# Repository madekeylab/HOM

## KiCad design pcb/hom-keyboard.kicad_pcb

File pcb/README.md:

# HOM-104 풀배열 키보드 PCB (rev 0.1)

사진 속 풀배열 기판을 바탕으로 새로 설계한 KiCad 7 프로젝트입니다.
배열과 기능(키마다 스위치, 다이오드, LED, 저항)은 원본과 같고, MCU와 회로는 새로 설계했습니다.

| 항목 | 내용 |
|---|---|
| 배열 | ANSI 104키 표준 풀배열, 키 간격 19.05 mm |
| 기판 크기 | 434.6 × 129.8 mm, 2층, 모서리 R2 |
| 매트릭스 | 6행 × 21열, COL2ROW, 키마다 1N4148W 다이오드 |
| 스위치 | Cherry MX 호환 PCB 마운트 (5핀). 2u, 2.25u, 2.75u, 6.25u 스태빌라이저 구멍 포함 |
| 백라이트 | 키마다 3 mm LED + 1 kΩ, AO3400A MOSFET으로 PWM 밝기 조절 (전체 약 210 mA) |
| MCU | RP2040 + W25Q128JVS 16 MB 플래시 + 12 MHz 크리스털 |
| USB | USB-C (HRO TYPE-C-31-M-12), USBLC6 ESD 보호, 500 mA 폴리퓨즈, AP2112K 3.3 V LDO |
| 기타 | BOOT/RESET 버튼, SWD 3핀 헤더, Caps/Num Lock 표시 LED, M2 마운팅홀 12개 |
| 펌웨어 | QMK (`firmware/qmk/hom104`) |

부품 배치: 스위치와 LED(THT)는 윗면, SMD 부품은 모두 뒷면에 있습니다.
MCU부는 사진의 기판처럼 넘패드 위 빈 공간에 모았습니다.

## 파일

- `hom-keyboard.kicad_pro / .kicad_sch / .kicad_pcb`: KiCad 7 프로젝트
- `hom-keyboard-schematic.pdf`: 회로도 PDF
- `hom-keyboard-bom.csv`: 부품 목록
- `docs/`: 회로도와 PCB 미리보기 이미지
- `firmware/qmk/hom104/`: QMK 키보드 정의 (`keyboard.json`, 기본 키맵)
- `tools/`: 생성 스크립트

## 다시 생성하기

```sh
# KiCad 7 (pcbnew 파이썬 모듈 포함)이 필요합니다
/usr/bin/python3 tools/build.py            # 회로도, PCB 배치, QMK 설정 생성
/usr/bin/python3 tools/verify_netlist.py   # KiCad 넷리스트를 설계와 대조
/usr/bin/python3 tools/drc.py hom-keyboard.kicad_pcb build/drc.txt
/usr/bin/python3 tools/route.py freerouting-1.9.0.jar   # 자동 배선 + GND 면 채우기
```

`build.py`는 먼저 회로도를 쓰고, KiCad가 그 회로도에서 뽑은 넷리스트로 PCB를 만듭니다.
그래서 회로도와 PCB의 연결은 항상 일치합니다.

## 현재 상태

- [x] 회로도 (넷리스트 검증 오류 0)
- [x] PCB 외곽, 부품 배치, 넷 연결, 마운팅홀 (배치 DRC: 겹침과 간격 오류 0)
- [x] QMK 펌웨어 설정
- [ ] 자동 배선 (Freerouting): 아직 안 함
- [ ] 거버 출력과 제작 주문

## 원본과 다른 점

- 사진만으로는 칩 모델을 읽을 수 없어서 MCU와 LED 구동부를 RP2040 기반으로 새로 설계했습니다.
- 뒷면 배선은 원본을 복제한 것이 아니고 새로 배선합니다.
- 외곽과 나사 구멍은 표준 치수로 잡았습니다. 기존 케이스에 맞추려면 실측값으로 `tools/build.py`의 `MARGIN`과 마운팅홀 위치(`add_mounting_holes`)를 수정하세요.

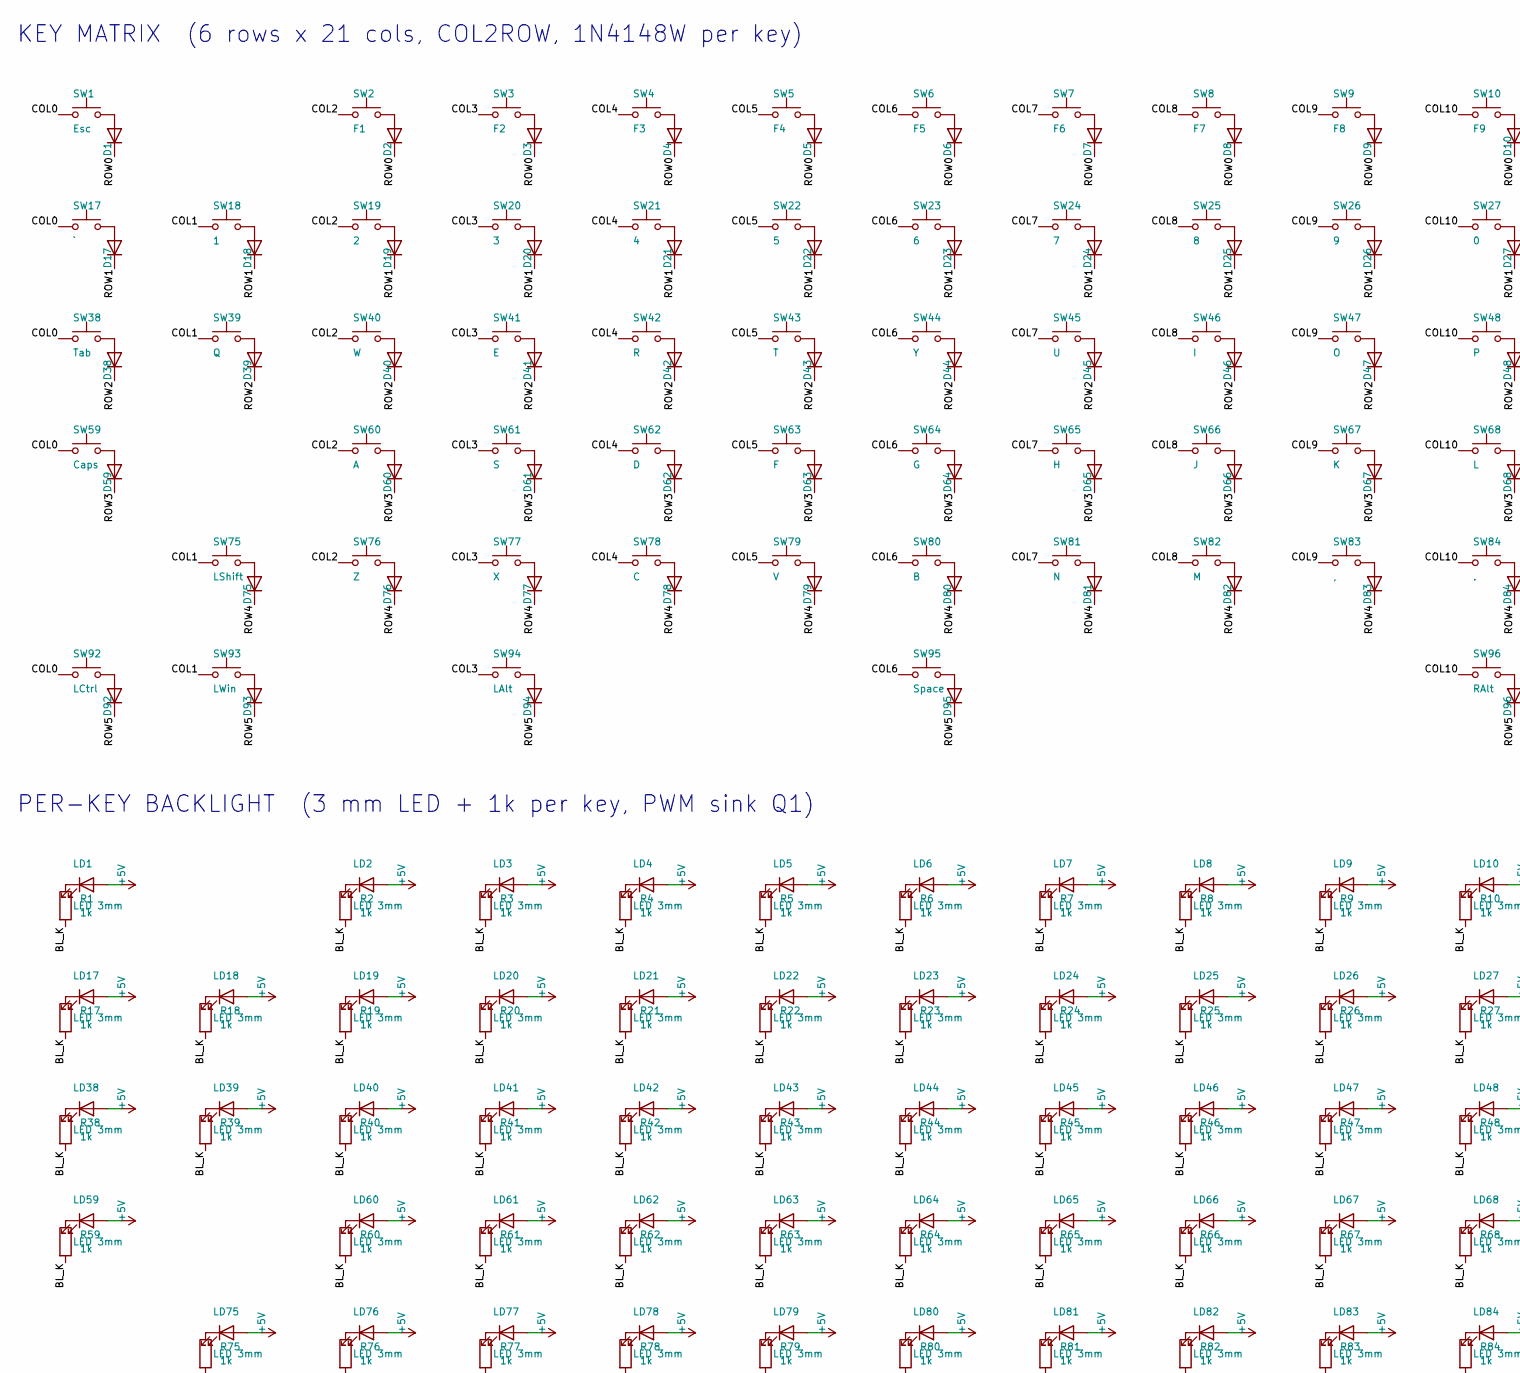
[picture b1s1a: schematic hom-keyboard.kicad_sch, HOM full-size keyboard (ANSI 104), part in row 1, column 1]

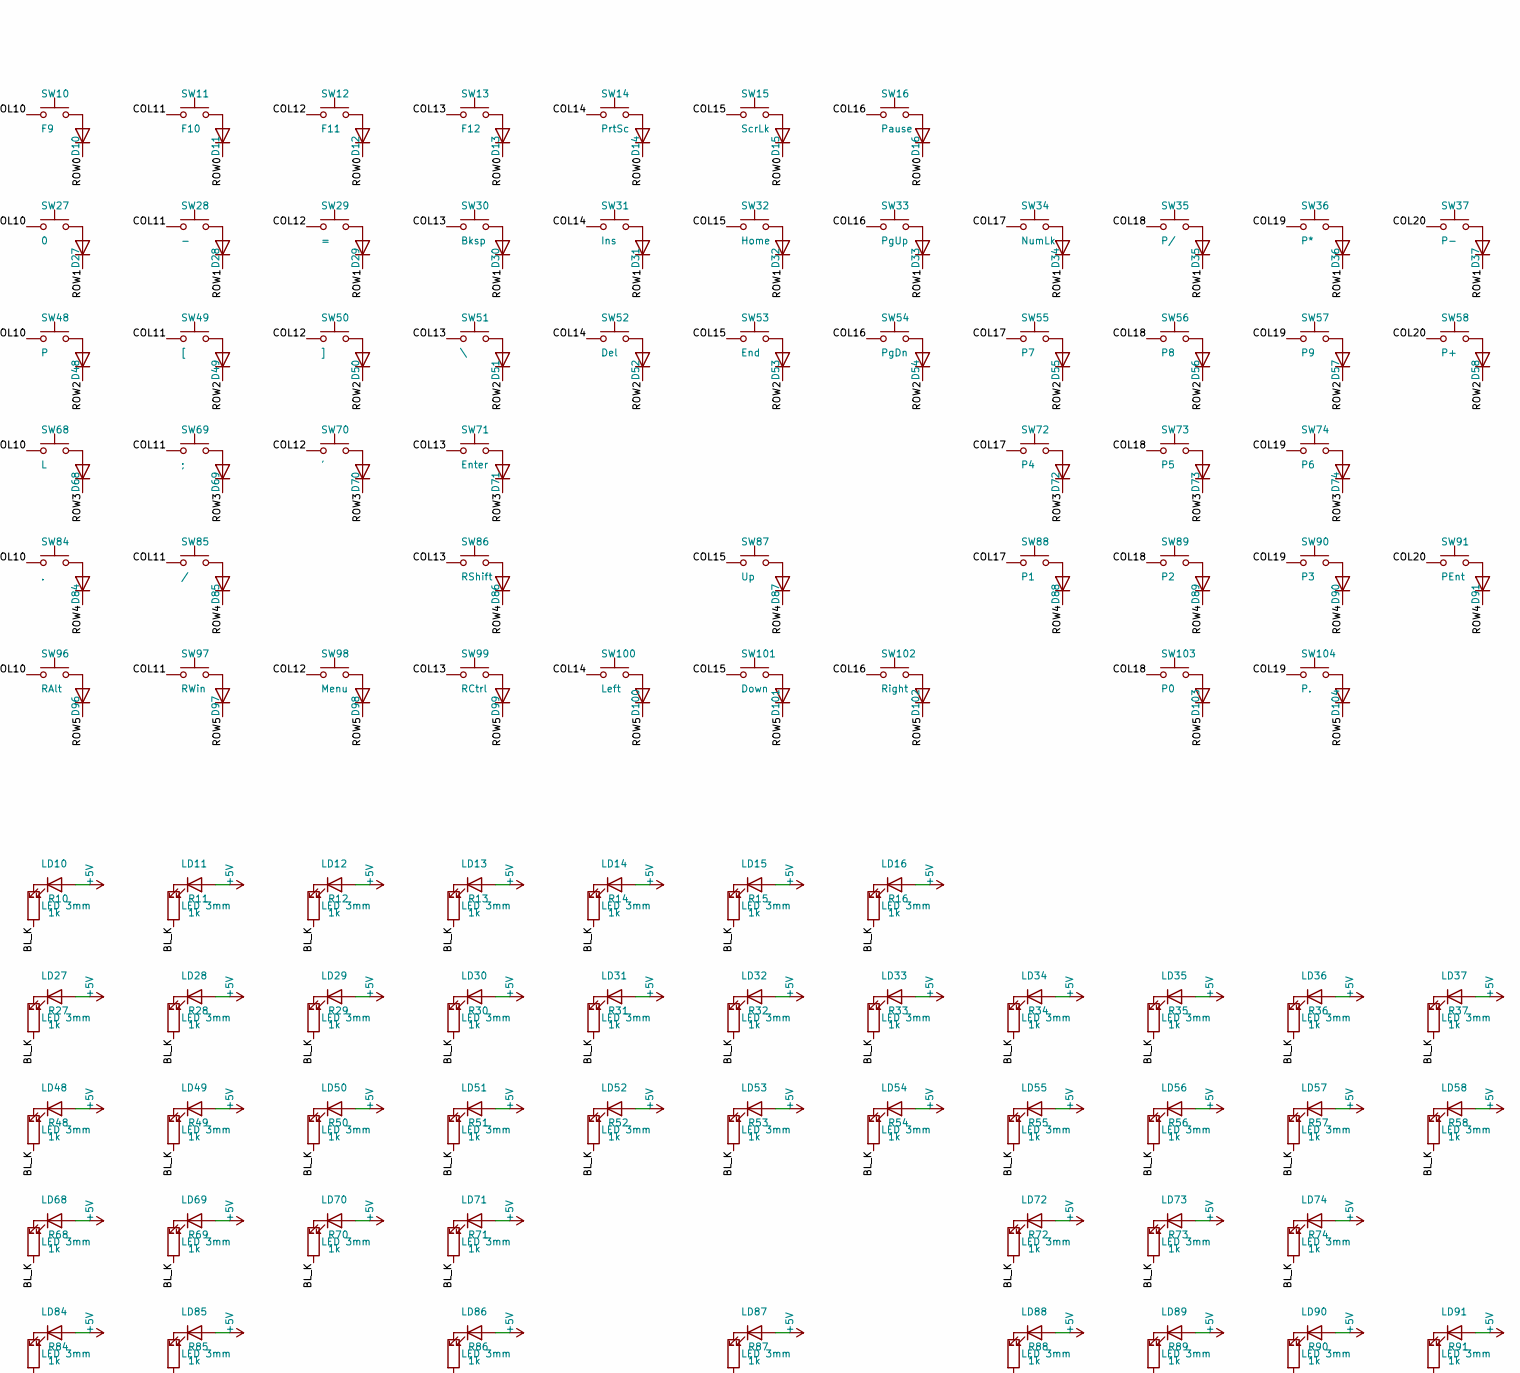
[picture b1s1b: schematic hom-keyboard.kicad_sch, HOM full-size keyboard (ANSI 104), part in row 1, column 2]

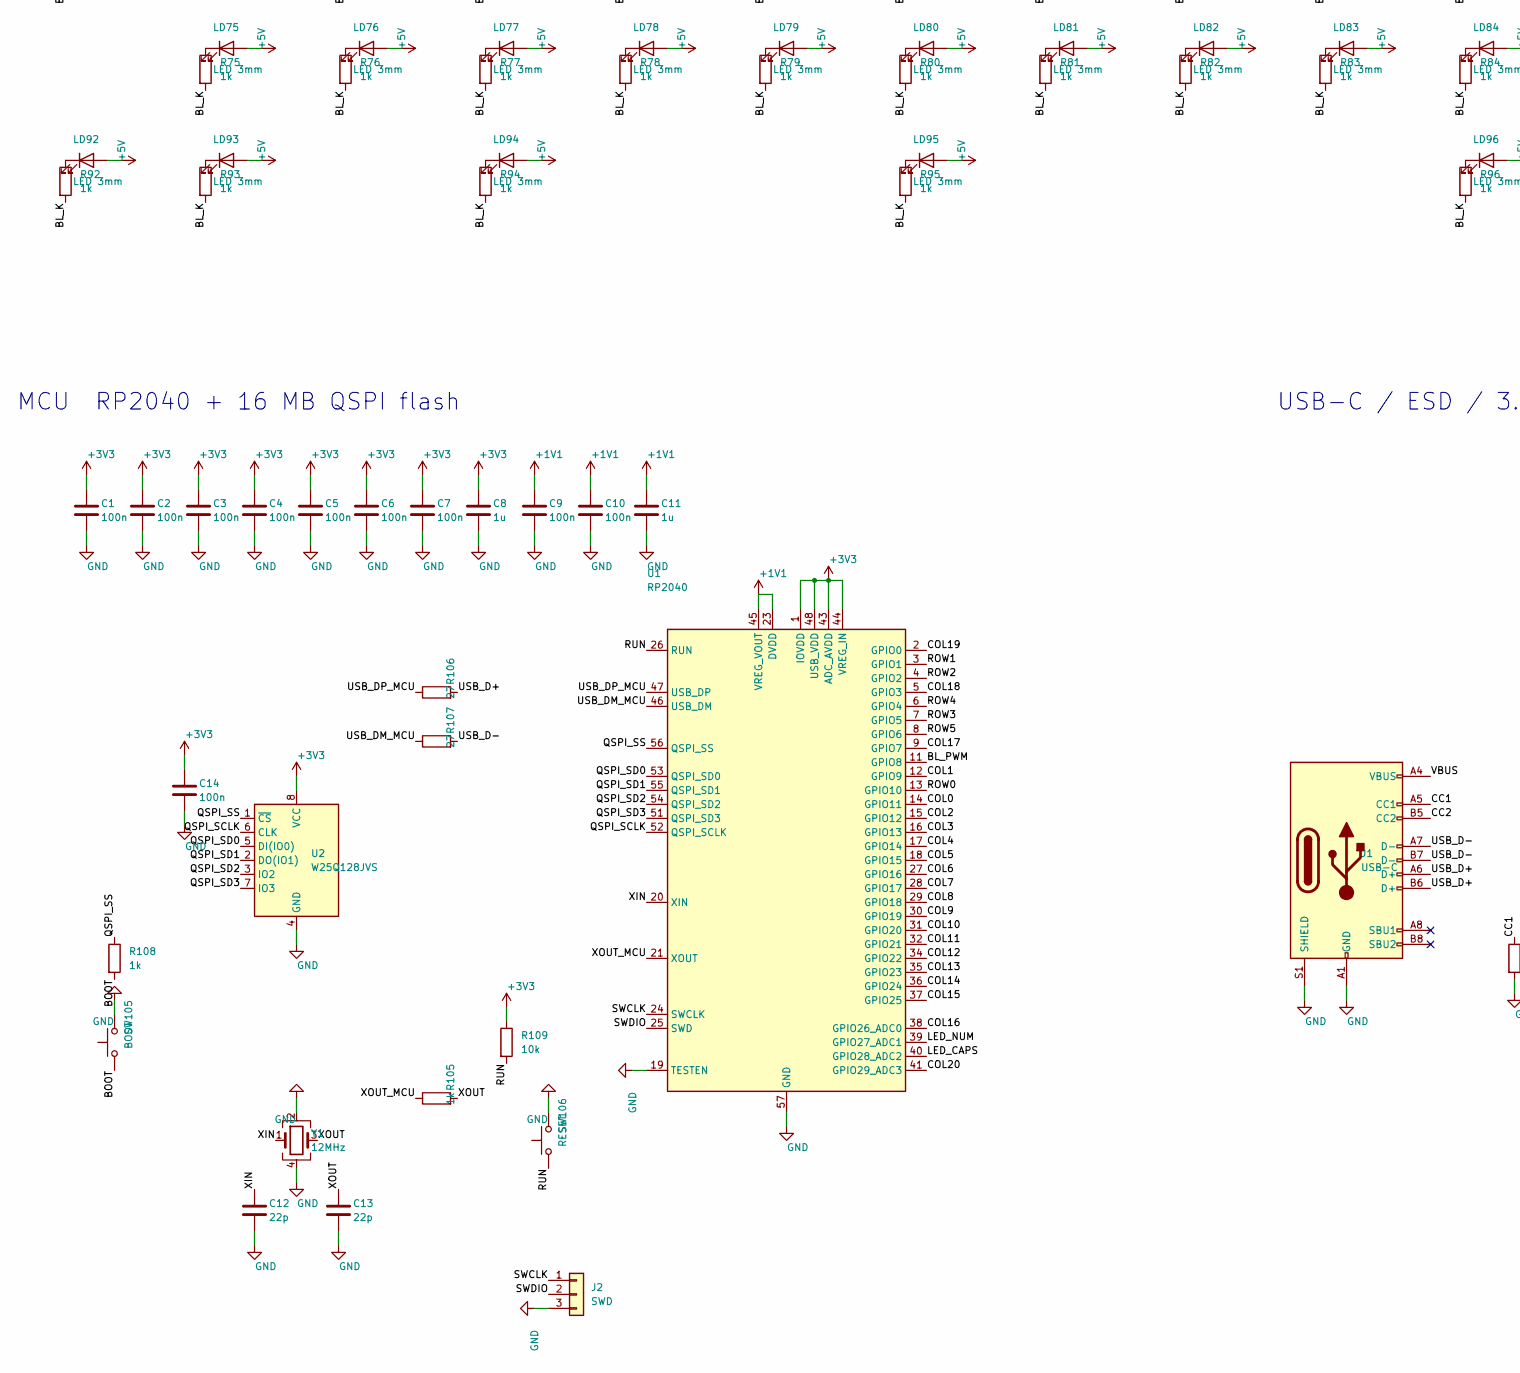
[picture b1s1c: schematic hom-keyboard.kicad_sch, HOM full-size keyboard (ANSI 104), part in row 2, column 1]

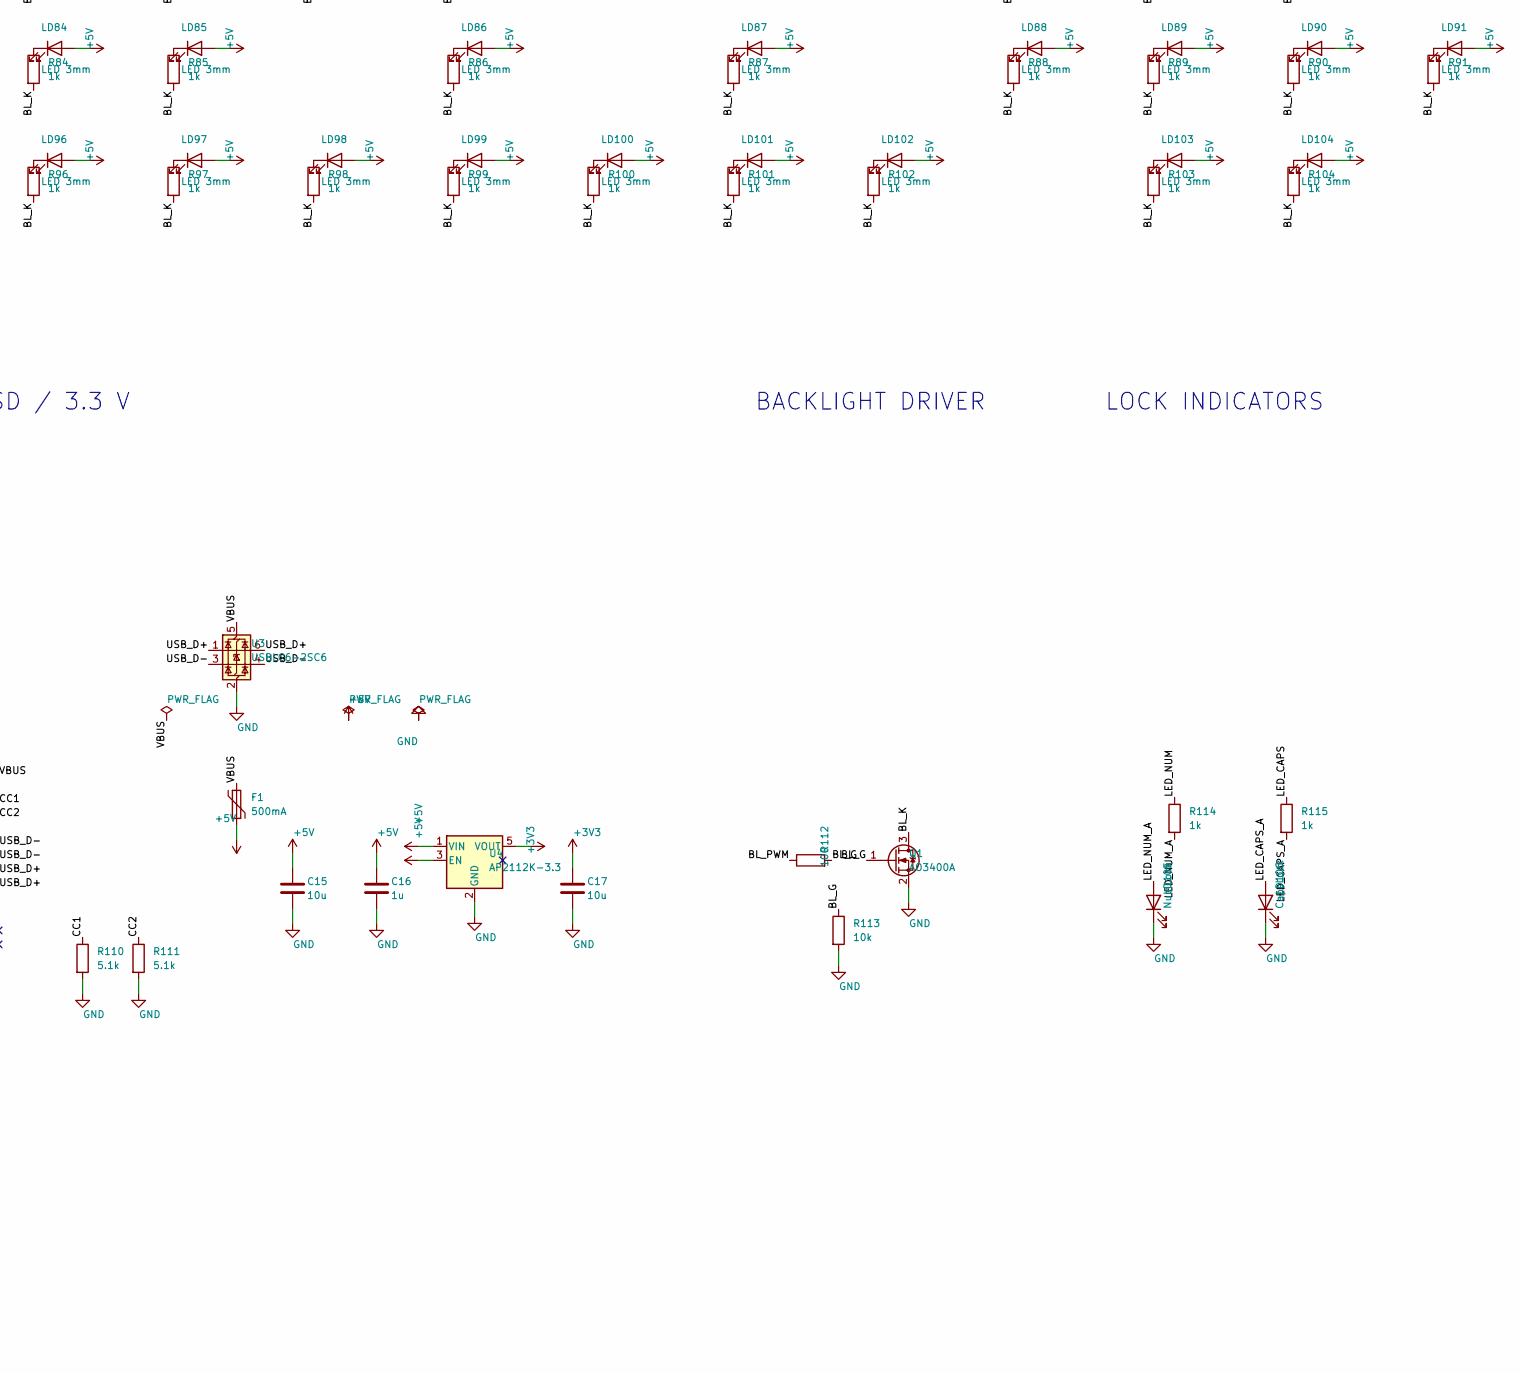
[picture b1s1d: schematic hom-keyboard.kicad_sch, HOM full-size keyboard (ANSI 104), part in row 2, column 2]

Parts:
C1, C2, C3, C4, C5, C6, C7, C9, C10, C14: 100n; C_0603_1608Metric
C8, C11, C16: 1u; C_0603_1608Metric
C12, C13: 22p; C_0603_1608Metric
C15, C17: 10u; C_0805_2012Metric
D1, D2, D3, D4, D5, D6, D7, D8, D9, D10, D11, D12, D13, D14, D15, D16, D17, D18, D19, D20, D21, D22, D23, D24, D25, D26, D27, D28, D29, D30, D31, D32, D33, D34, D35, D36, D37, D38, D39, D40, D41, D42, D43, D44, D45, D46, D47, D48, D49, D50, D51, D52, D53, D54, D55, D56, D57, D58, D59, D60, D61, D62, D63, D64, D65, D66, D67, D68, D69, D70, D71, D72, D73, D74, D75, D76, D77, D78, D79, D80, D81, D82, D83, D84, D85, D86, D87, D88, D89, D90, D91, D92, D93, D94, D95, D96, D97, D98, D99, D100, D101, D102, D103, D104: 1N4148W; D_SOD-123
F1: 500mA; Fuse_1206_3216Metric
J1: USB-C; USB_C_Receptacle_HRO_TYPE-C-31-M-12
J2: SWD; PinHeader_1x03_P2.54mm_Vertical
LD1, LD2, LD3, LD4, LD5, LD6, LD7, LD8, LD9, LD10, LD11, LD12, LD13, LD14, LD15, LD16, LD17, LD18, LD19, LD20, LD21, LD22, LD23, LD24, LD25, LD26, LD27, LD28, LD29, LD30, LD31, LD32, LD33, LD34, LD35, LD36, LD37, LD38, LD39, LD40, LD41, LD42, LD43, LD44, LD45, LD46, LD47, LD48, LD49, LD50, LD51, LD52, LD53, LD54, LD55, LD56, LD57, LD58, LD59, LD60, LD61, LD62, LD63, LD64, LD65, LD66, LD67, LD68, LD69, LD70, LD71, LD72, LD73, LD74, LD75, LD76, LD77, LD78, LD79, LD80, LD81, LD82, LD83, LD84, LD85, LD86, LD87, LD88, LD89, LD90, LD91, LD92, LD93, LD94, LD95, LD96, LD97, LD98, LD99, LD100, LD101, LD102, LD103, LD104: LED 3mm; LED_D3.0mm
LD105: NumLock; LED_D3.0mm
LD106: CapsLock; LED_D3.0mm
Q1: AO3400A; SOT-23
R1, R2, R3, R4, R5, R6, R7, R8, R9, R10, R11, R12, R13, R14, R15, R16, R17, R18, R19, R20, R21, R22, R23, R24, R25, R26, R27, R28, R29, R30, R31, R32, R33, R34, R35, R36, R37, R38, R39, R40, R41, R42, R43, R44, R45, R46, R47, R48, R49, R50, R51, R52, R53, R54, R55, R56, R57, R58, R59, R60, R61, R62, R63, R64, R65, R66, R67, R68, R69, R70, R71, R72, R73, R74, R75, R76, R77, R78, R79, R80, R81, R82, R83, R84, R85, R86, R87, R88, R89, R90, R91, R92, R93, R94, R95, R96, R97, R98, R99, R100, R101, R102, R103, R104, R105, R108, R114, R115: 1k; R_0603_1608Metric
R106, R107: 27; R_0603_1608Metric
R109, R113: 10k; R_0603_1608Metric
R110, R111: 5.1k; R_0603_1608Metric
R112: 100; R_0603_1608Metric
SW1: Esc; SW_Cherry_MX_1.00u_PCB
SW2: F1; SW_Cherry_MX_1.00u_PCB
SW3: F2; SW_Cherry_MX_1.00u_PCB
SW4: F3; SW_Cherry_MX_1.00u_PCB
SW5: F4; SW_Cherry_MX_1.00u_PCB
SW6: F5; SW_Cherry_MX_1.00u_PCB
SW7: F6; SW_Cherry_MX_1.00u_PCB
SW8: F7; SW_Cherry_MX_1.00u_PCB
SW9: F8; SW_Cherry_MX_1.00u_PCB
SW10: F9; SW_Cherry_MX_1.00u_PCB
SW11: F10; SW_Cherry_MX_1.00u_PCB
SW12: F11; SW_Cherry_MX_1.00u_PCB
SW13: F12; SW_Cherry_MX_1.00u_PCB
SW14: PrtSc; SW_Cherry_MX_1.00u_PCB
SW15: ScrLk; SW_Cherry_MX_1.00u_PCB
SW16: Pause; SW_Cherry_MX_1.00u_PCB
SW17: `; SW_Cherry_MX_1.00u_PCB
SW18: 1; SW_Cherry_MX_1.00u_PCB
SW19: 2; SW_Cherry_MX_1.00u_PCB
SW20: 3; SW_Cherry_MX_1.00u_PCB
SW21: 4; SW_Cherry_MX_1.00u_PCB
SW22: 5; SW_Cherry_MX_1.00u_PCB
SW23: 6; SW_Cherry_MX_1.00u_PCB
SW24: 7; SW_Cherry_MX_1.00u_PCB
SW25: 8; SW_Cherry_MX_1.00u_PCB
SW26: 9; SW_Cherry_MX_1.00u_PCB
SW27: 0; SW_Cherry_MX_1.00u_PCB
SW28: -; SW_Cherry_MX_1.00u_PCB
SW29: =; SW_Cherry_MX_1.00u_PCB
SW30: Bksp; SW_Cherry_MX_2.00u_PCB
SW31: Ins; SW_Cherry_MX_1.00u_PCB
SW32: Home; SW_Cherry_MX_1.00u_PCB
SW33: PgUp; SW_Cherry_MX_1.00u_PCB
SW34: NumLk; SW_Cherry_MX_1.00u_PCB
SW35: P/; SW_Cherry_MX_1.00u_PCB
SW36: P*; SW_Cherry_MX_1.00u_PCB
SW37: P-; SW_Cherry_MX_1.00u_PCB
SW38: Tab; SW_Cherry_MX_1.50u_PCB
SW39: Q; SW_Cherry_MX_1.00u_PCB
SW40: W; SW_Cherry_MX_1.00u_PCB
SW41: E; SW_Cherry_MX_1.00u_PCB
SW42: R; SW_Cherry_MX_1.00u_PCB
SW43: T; SW_Cherry_MX_1.00u_PCB
SW44: Y; SW_Cherry_MX_1.00u_PCB
SW45: U; SW_Cherry_MX_1.00u_PCB
SW46: I; SW_Cherry_MX_1.00u_PCB
SW47: O; SW_Cherry_MX_1.00u_PCB
SW48: P; SW_Cherry_MX_1.00u_PCB
SW49: [; SW_Cherry_MX_1.00u_PCB
SW50: ]; SW_Cherry_MX_1.00u_PCB
SW51: \; SW_Cherry_MX_1.50u_PCB
SW52: Del; SW_Cherry_MX_1.00u_PCB
SW53: End; SW_Cherry_MX_1.00u_PCB
SW54: PgDn; SW_Cherry_MX_1.00u_PCB
SW55: P7; SW_Cherry_MX_1.00u_PCB
SW56: P8; SW_Cherry_MX_1.00u_PCB
SW57: P9; SW_Cherry_MX_1.00u_PCB
SW58: P+; SW_Cherry_MX_2.00u_Vertical_PCB
SW59: Caps; SW_Cherry_MX_1.75u_PCB
SW60: A; SW_Cherry_MX_1.00u_PCB
SW61: S; SW_Cherry_MX_1.00u_PCB
SW62: D; SW_Cherry_MX_1.00u_PCB
SW63: F; SW_Cherry_MX_1.00u_PCB
SW64: G; SW_Cherry_MX_1.00u_PCB
SW65: H; SW_Cherry_MX_1.00u_PCB
SW66: J; SW_Cherry_MX_1.00u_PCB
SW67: K; SW_Cherry_MX_1.00u_PCB
SW68: L; SW_Cherry_MX_1.00u_PCB
SW69: ;; SW_Cherry_MX_1.00u_PCB
SW70: '; SW_Cherry_MX_1.00u_PCB
SW71: Enter; SW_Cherry_MX_2.25u_PCB
SW72: P4; SW_Cherry_MX_1.00u_PCB
SW73: P5; SW_Cherry_MX_1.00u_PCB
SW74: P6; SW_Cherry_MX_1.00u_PCB
SW75: LShift; SW_Cherry_MX_2.25u_PCB
SW76: Z; SW_Cherry_MX_1.00u_PCB
SW77: X; SW_Cherry_MX_1.00u_PCB
SW78: C; SW_Cherry_MX_1.00u_PCB
SW79: V; SW_Cherry_MX_1.00u_PCB
SW80: B; SW_Cherry_MX_1.00u_PCB
SW81: N; SW_Cherry_MX_1.00u_PCB
SW82: M; SW_Cherry_MX_1.00u_PCB
SW83: ,; SW_Cherry_MX_1.00u_PCB
SW84: .; SW_Cherry_MX_1.00u_PCB
SW85: /; SW_Cherry_MX_1.00u_PCB
SW86: RShift; SW_Cherry_MX_2.75u_PCB
SW87: Up; SW_Cherry_MX_1.00u_PCB
SW88: P1; SW_Cherry_MX_1.00u_PCB
SW89: P2; SW_Cherry_MX_1.00u_PCB
SW90: P3; SW_Cherry_MX_1.00u_PCB
SW91: PEnt; SW_Cherry_MX_2.00u_Vertical_PCB
SW92: LCtrl; SW_Cherry_MX_1.25u_PCB
SW93: LWin; SW_Cherry_MX_1.25u_PCB
SW94: LAlt; SW_Cherry_MX_1.25u_PCB
SW95: Space; SW_Cherry_MX_6.25u_PCB
SW96: RAlt; SW_Cherry_MX_1.25u_PCB
SW97: RWin; SW_Cherry_MX_1.25u_PCB
SW98: Menu; SW_Cherry_MX_1.25u_PCB
SW99: RCtrl; SW_Cherry_MX_1.25u_PCB
SW100: Left; SW_Cherry_MX_1.00u_PCB
SW101: Down; SW_Cherry_MX_1.00u_PCB
SW102: Right; SW_Cherry_MX_1.00u_PCB
SW103: P0; SW_Cherry_MX_2.00u_PCB
SW104: P.; SW_Cherry_MX_1.00u_PCB
SW105: BOOT; SW_SPST_TL3342
SW106: RESET; SW_SPST_TL3342
U1: RP2040; QFN-56-1EP_7x7mm_P0.4mm_EP3.2x3.2mm_ThermalVias
U2: W25Q128JVS; SOIC-8_5.23x5.23mm_P1.27mm
U3: USBLC6-2SC6; SOT-23-6
U4: AP2112K-3.3; SOT-23-5
Y1: 12MHz; Crystal_SMD_3225-4Pin_3.2x2.5mm

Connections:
+1V1: C9.1, C10.1, C11.1, U1.23 (DVDD), U1.45 (VREG_VOUT), U1.50 (DVDD)
+3V3: C1.1, C2.1, C3.1, C4.1, C5.1, C6.1, C7.1, C8.1, C14.1, C17.1, R109.1, U1.1 (IOVDD), U1.10 (IOVDD), U1.22 (IOVDD), U1.33 (IOVDD), U1.42 (IOVDD), U1.43 (ADC_AVDD), U1.44 (VREG_IN), U1.48 (USB_VDD), U1.49 (IOVDD), U2.8 (VCC), U4.5 (VOUT)
+5V: C15.1, C16.1, F1.2, LD1.2 (A), LD2.2 (A), LD3.2 (A), LD4.2 (A), LD5.2 (A), LD6.2 (A), LD7.2 (A), LD8.2 (A), LD9.2 (A), LD10.2 (A), LD11.2 (A), LD12.2 (A), LD13.2 (A), LD14.2 (A), LD15.2 (A), LD16.2 (A), LD17.2 (A), LD18.2 (A), LD19.2 (A), LD20.2 (A), LD21.2 (A), LD22.2 (A), LD23.2 (A), LD24.2 (A), LD25.2 (A), LD26.2 (A), LD27.2 (A), LD28.2 (A), LD29.2 (A), LD30.2 (A), LD31.2 (A), LD32.2 (A), LD33.2 (A), LD34.2 (A), LD35.2 (A), LD36.2 (A), LD37.2 (A), LD38.2 (A), LD39.2 (A), LD40.2 (A), LD41.2 (A), LD42.2 (A), LD43.2 (A), LD44.2 (A), LD45.2 (A), LD46.2 (A), LD47.2 (A), LD48.2 (A), LD49.2 (A), LD50.2 (A), LD51.2 (A), LD52.2 (A), LD53.2 (A), LD54.2 (A), LD55.2 (A), LD56.2 (A), LD57.2 (A), LD58.2 (A), LD59.2 (A), LD60.2 (A), LD61.2 (A), LD62.2 (A), LD63.2 (A), LD64.2 (A), LD65.2 (A), LD66.2 (A), LD67.2 (A), LD68.2 (A), LD69.2 (A), LD70.2 (A), LD71.2 (A), LD72.2 (A), LD73.2 (A), LD74.2 (A), LD75.2 (A), LD76.2 (A), LD77.2 (A), LD78.2 (A), LD79.2 (A), LD80.2 (A), LD81.2 (A), LD82.2 (A), LD83.2 (A), LD84.2 (A), LD85.2 (A), LD86.2 (A), LD87.2 (A), LD88.2 (A), LD89.2 (A), LD90.2 (A), LD91.2 (A), LD92.2 (A), LD93.2 (A), LD94.2 (A), LD95.2 (A), LD96.2 (A), LD97.2 (A), LD98.2 (A), LD99.2 (A), LD100.2 (A), LD101.2 (A), LD102.2 (A), LD103.2 (A), LD104.2 (A), U4.1 (VIN), U4.3 (EN)
/BL_G: Q1.1 (G), R112.2, R113.1
/BL_K: Q1.3 (D), R1.2, R2.2, R3.2, R4.2, R5.2, R6.2, R7.2, R8.2, R9.2, R10.2, R11.2, R12.2, R13.2, R14.2, R15.2, R16.2, R17.2, R18.2, R19.2, R20.2, R21.2, R22.2, R23.2, R24.2, R25.2, R26.2, R27.2, R28.2, R29.2, R30.2, R31.2, R32.2, R33.2, R34.2, R35.2, R36.2, R37.2, R38.2, R39.2, R40.2, R41.2, R42.2, R43.2, R44.2, R45.2, R46.2, R47.2, R48.2, R49.2, R50.2, R51.2, R52.2, R53.2, R54.2, R55.2, R56.2, R57.2, R58.2, R59.2, R60.2, R61.2, R62.2, R63.2, R64.2, R65.2, R66.2, R67.2, R68.2, R69.2, R70.2, R71.2, R72.2, R73.2, R74.2, R75.2, R76.2, R77.2, R78.2, R79.2, R80.2, R81.2, R82.2, R83.2, R84.2, R85.2, R86.2, R87.2, R88.2, R89.2, R90.2, R91.2, R92.2, R93.2, R94.2, R95.2, R96.2, R97.2, R98.2, R99.2, R100.2, R101.2, R102.2, R103.2, R104.2
/BL_PWM: R112.1, U1.11 (GPIO8)
/BOOT: R108.2, SW105.1
/CC1: J1.A5 (CC1), R110.1
/CC2: J1.B5 (CC2), R111.1
/COL0: SW1.1, SW17.1, SW38.1, SW59.1, SW92.1, U1.14 (GPIO11)
/COL1: SW18.1, SW39.1, SW75.1, SW93.1, U1.12 (GPIO9)
/COL2: SW2.1, SW19.1, SW40.1, SW60.1, SW76.1, U1.15 (GPIO12)
/COL3: SW3.1, SW20.1, SW41.1, SW61.1, SW77.1, SW94.1, U1.16 (GPIO13)
/COL4: SW4.1, SW21.1, SW42.1, SW62.1, SW78.1, U1.17 (GPIO14)
/COL5: SW5.1, SW22.1, SW43.1, SW63.1, SW79.1, U1.18 (GPIO15)
/COL6: SW6.1, SW23.1, SW44.1, SW64.1, SW80.1, SW95.1, U1.27 (GPIO16)
/COL7: SW7.1, SW24.1, SW45.1, SW65.1, SW81.1, U1.28 (GPIO17)
/COL8: SW8.1, SW25.1, SW46.1, SW66.1, SW82.1, U1.29 (GPIO18)
/COL9: SW9.1, SW26.1, SW47.1, SW67.1, SW83.1, U1.30 (GPIO19)
/COL10: SW10.1, SW27.1, SW48.1, SW68.1, SW84.1, SW96.1, U1.31 (GPIO20)
/COL11: SW11.1, SW28.1, SW49.1, SW69.1, SW85.1, SW97.1, U1.32 (GPIO21)
/COL12: SW12.1, SW29.1, SW50.1, SW70.1, SW98.1, U1.34 (GPIO22)
/COL13: SW13.1, SW30.1, SW51.1, SW71.1, SW86.1, SW99.1, U1.35 (GPIO23)
/COL14: SW14.1, SW31.1, SW52.1, SW100.1, U1.36 (GPIO24)
/COL15: SW15.1, SW32.1, SW53.1, SW87.1, SW101.1, U1.37 (GPIO25)
/COL16: SW16.1, SW33.1, SW54.1, SW102.1, U1.38 (GPIO26_ADC0)
/COL17: SW34.1, SW55.1, SW72.1, SW88.1, U1.9 (GPIO7)
/COL18: SW35.1, SW56.1, SW73.1, SW89.1, SW103.1, U1.5 (GPIO3)
/COL19: SW36.1, SW57.1, SW74.1, SW90.1, SW104.1, U1.2 (GPIO0)
/COL20: SW37.1, SW58.1, SW91.1, U1.41 (GPIO29_ADC3)
/LED_CAPS: R115.1, U1.40 (GPIO28_ADC2)
/LED_CAPS_A: LD106.2 (A), R115.2
/LED_NUM: R114.1, U1.39 (GPIO27_ADC1)
/LED_NUM_A: LD105.2 (A), R114.2
/QSPI_SCLK: U1.52 (QSPI_SCLK), U2.6 (CLK)
/QSPI_SD0: U1.53 (QSPI_SD0), U2.5 (DI(IO0))
/QSPI_SD1: U1.55 (QSPI_SD1), U2.2 (DO(IO1))
/QSPI_SD2: U1.54 (QSPI_SD2), U2.3 (IO2)
/QSPI_SD3: U1.51 (QSPI_SD3), U2.7 (IO3)
/QSPI_SS: R108.1, U1.56 (QSPI_SS), U2.1 (~CS)
/ROW0: D1.1 (K), D2.1 (K), D3.1 (K), D4.1 (K), D5.1 (K), D6.1 (K), D7.1 (K), D8.1 (K), D9.1 (K), D10.1 (K), D11.1 (K), D12.1 (K), D13.1 (K), D14.1 (K), D15.1 (K), D16.1 (K), U1.13 (GPIO10)
/ROW1: D17.1 (K), D18.1 (K), D19.1 (K), D20.1 (K), D21.1 (K), D22.1 (K), D23.1 (K), D24.1 (K), D25.1 (K), D26.1 (K), D27.1 (K), D28.1 (K), D29.1 (K), D30.1 (K), D31.1 (K), D32.1 (K), D33.1 (K), D34.1 (K), D35.1 (K), D36.1 (K), D37.1 (K), U1.3 (GPIO1)
/ROW2: D38.1 (K), D39.1 (K), D40.1 (K), D41.1 (K), D42.1 (K), D43.1 (K), D44.1 (K), D45.1 (K), D46.1 (K), D47.1 (K), D48.1 (K), D49.1 (K), D50.1 (K), D51.1 (K), D52.1 (K), D53.1 (K), D54.1 (K), D55.1 (K), D56.1 (K), D57.1 (K), D58.1 (K), U1.4 (GPIO2)
/ROW3: D59.1 (K), D60.1 (K), D61.1 (K), D62.1 (K), D63.1 (K), D64.1 (K), D65.1 (K), D66.1 (K), D67.1 (K), D68.1 (K), D69.1 (K), D70.1 (K), D71.1 (K), D72.1 (K), D73.1 (K), D74.1 (K), U1.7 (GPIO5)
/ROW4: D75.1 (K), D76.1 (K), D77.1 (K), D78.1 (K), D79.1 (K), D80.1 (K), D81.1 (K), D82.1 (K), D83.1 (K), D84.1 (K), D85.1 (K), D86.1 (K), D87.1 (K), D88.1 (K), D89.1 (K), D90.1 (K), D91.1 (K), U1.6 (GPIO4)
/ROW5: D92.1 (K), D93.1 (K), D94.1 (K), D95.1 (K), D96.1 (K), D97.1 (K), D98.1 (K), D99.1 (K), D100.1 (K), D101.1 (K), D102.1 (K), D103.1 (K), D104.1 (K), U1.8 (GPIO6)
/RUN: R109.2, SW106.1, U1.26 (RUN)
/SWCLK: J2.1, U1.24 (SWCLK)
/SWDIO: J2.2, U1.25 (SWD)
/USB_D+: J1.A6 (D+), J1.B6 (D+), R106.2, U3.1 (I/O1), U3.6 (I/O1)
/USB_D-: J1.A7 (D-), J1.B7 (D-), R107.2, U3.3 (I/O2), U3.4 (I/O2)
/USB_DM_MCU: R107.1, U1.46 (USB_DM)
/USB_DP_MCU: R106.1, U1.47 (USB_DP)
/VBUS: F1.1, J1.A4 (VBUS), J1.A9 (VBUS), J1.B4 (VBUS), J1.B9 (VBUS), U3.5 (VBUS)
/XIN: C12.1, U1.20 (XIN), Y1.1
/XOUT: C13.1, R105.2, Y1.3
/XOUT_MCU: R105.1, U1.21 (XOUT)
GND: C1.2, C2.2, C3.2, C4.2, C5.2, C6.2, C7.2, C8.2, C9.2, C10.2, C11.2, C12.2, C13.2, C14.2, C15.2, C16.2, C17.2, J1.A1 (GND), J1.A12 (GND), J1.B1 (GND), J1.B12 (GND), J1.S1 (SHIELD), J2.3, LD105.1 (K), LD106.1 (K), Q1.2 (S), R110.2, R111.2, R113.2, SW105.2, SW106.2, U1.19 (TESTEN), U1.57 (GND), U2.4 (GND), U3.2 (GND), U4.2 (GND), Y1.2, Y1.4
unnamed: D1.2 (A), SW1.2
unnamed: D2.2 (A), SW2.2
unnamed: D3.2 (A), SW3.2
unnamed: D4.2 (A), SW4.2
unnamed: D5.2 (A), SW5.2
unnamed: D6.2 (A), SW6.2
unnamed: D7.2 (A), SW7.2
unnamed: D8.2 (A), SW8.2
unnamed: D9.2 (A), SW9.2
unnamed: D10.2 (A), SW10.2
unnamed: D11.2 (A), SW11.2
unnamed: D12.2 (A), SW12.2
unnamed: D13.2 (A), SW13.2
unnamed: D14.2 (A), SW14.2
unnamed: D15.2 (A), SW15.2
unnamed: D16.2 (A), SW16.2
unnamed: D17.2 (A), SW17.2
unnamed: D18.2 (A), SW18.2
unnamed: D19.2 (A), SW19.2
unnamed: D20.2 (A), SW20.2
unnamed: D21.2 (A), SW21.2
unnamed: D22.2 (A), SW22.2
unnamed: D23.2 (A), SW23.2
unnamed: D24.2 (A), SW24.2
unnamed: D25.2 (A), SW25.2
unnamed: D26.2 (A), SW26.2
unnamed: D27.2 (A), SW27.2
unnamed: D28.2 (A), SW28.2
unnamed: D29.2 (A), SW29.2
unnamed: D30.2 (A), SW30.2
unnamed: D31.2 (A), SW31.2
unnamed: D32.2 (A), SW32.2
unnamed: D33.2 (A), SW33.2
unnamed: D34.2 (A), SW34.2
unnamed: D35.2 (A), SW35.2
unnamed: D36.2 (A), SW36.2
unnamed: D37.2 (A), SW37.2
unnamed: D38.2 (A), SW38.2
unnamed: D39.2 (A), SW39.2
unnamed: D40.2 (A), SW40.2
unnamed: D41.2 (A), SW41.2
unnamed: D42.2 (A), SW42.2
unnamed: D43.2 (A), SW43.2
unnamed: D44.2 (A), SW44.2
unnamed: D45.2 (A), SW45.2
unnamed: D46.2 (A), SW46.2
unnamed: D47.2 (A), SW47.2
unnamed: D48.2 (A), SW48.2
unnamed: D49.2 (A), SW49.2
unnamed: D50.2 (A), SW50.2
unnamed: D51.2 (A), SW51.2
unnamed: D52.2 (A), SW52.2
unnamed: D53.2 (A), SW53.2
unnamed: D54.2 (A), SW54.2
unnamed: D55.2 (A), SW55.2
unnamed: D56.2 (A), SW56.2
unnamed: D57.2 (A), SW57.2
unnamed: D58.2 (A), SW58.2
unnamed: D59.2 (A), SW59.2
unnamed: D60.2 (A), SW60.2
unnamed: D61.2 (A), SW61.2
unnamed: D62.2 (A), SW62.2
unnamed: D63.2 (A), SW63.2
unnamed: D64.2 (A), SW64.2
unnamed: D65.2 (A), SW65.2
unnamed: D66.2 (A), SW66.2
unnamed: D67.2 (A), SW67.2
unnamed: D68.2 (A), SW68.2
unnamed: D69.2 (A), SW69.2
unnamed: D70.2 (A), SW70.2
unnamed: D71.2 (A), SW71.2
unnamed: D72.2 (A), SW72.2
unnamed: D73.2 (A), SW73.2
unnamed: D74.2 (A), SW74.2
unnamed: D75.2 (A), SW75.2
unnamed: D76.2 (A), SW76.2
unnamed: D77.2 (A), SW77.2
unnamed: D78.2 (A), SW78.2
unnamed: D79.2 (A), SW79.2
unnamed: D80.2 (A), SW80.2
unnamed: D81.2 (A), SW81.2
unnamed: D82.2 (A), SW82.2
unnamed: D83.2 (A), SW83.2
unnamed: D84.2 (A), SW84.2
unnamed: D85.2 (A), SW85.2
unnamed: D86.2 (A), SW86.2
unnamed: D87.2 (A), SW87.2
unnamed: D88.2 (A), SW88.2
unnamed: D89.2 (A), SW89.2
unnamed: D90.2 (A), SW90.2
unnamed: D91.2 (A), SW91.2
unnamed: D92.2 (A), SW92.2
unnamed: D93.2 (A), SW93.2
unnamed: D94.2 (A), SW94.2
unnamed: D95.2 (A), SW95.2
unnamed: D96.2 (A), SW96.2
unnamed: D97.2 (A), SW97.2
unnamed: D98.2 (A), SW98.2
unnamed: D99.2 (A), SW99.2
unnamed: D100.2 (A), SW100.2
unnamed: D101.2 (A), SW101.2
unnamed: D102.2 (A), SW102.2
unnamed: D103.2 (A), SW103.2
unnamed: D104.2 (A), SW104.2
unnamed: LD1.1 (K), R1.1
unnamed: LD2.1 (K), R2.1
unnamed: LD3.1 (K), R3.1
unnamed: LD4.1 (K), R4.1
unnamed: LD5.1 (K), R5.1
unnamed: LD6.1 (K), R6.1
unnamed: LD7.1 (K), R7.1
unnamed: LD8.1 (K), R8.1
unnamed: LD9.1 (K), R9.1
unnamed: LD10.1 (K), R10.1
unnamed: LD11.1 (K), R11.1
unnamed: LD12.1 (K), R12.1
unnamed: LD13.1 (K), R13.1
unnamed: LD14.1 (K), R14.1
unnamed: LD15.1 (K), R15.1
unnamed: LD16.1 (K), R16.1
unnamed: LD17.1 (K), R17.1
unnamed: LD18.1 (K), R18.1
unnamed: LD19.1 (K), R19.1
unnamed: LD20.1 (K), R20.1
unnamed: LD21.1 (K), R21.1
unnamed: LD22.1 (K), R22.1
unnamed: LD23.1 (K), R23.1
unnamed: LD24.1 (K), R24.1
unnamed: LD25.1 (K), R25.1
unnamed: LD26.1 (K), R26.1
unnamed: LD27.1 (K), R27.1
unnamed: LD28.1 (K), R28.1
unnamed: LD29.1 (K), R29.1
unnamed: LD30.1 (K), R30.1
unnamed: LD31.1 (K), R31.1
unnamed: LD32.1 (K), R32.1
unnamed: LD33.1 (K), R33.1
unnamed: LD34.1 (K), R34.1
unnamed: LD35.1 (K), R35.1
unnamed: LD36.1 (K), R36.1
unnamed: LD37.1 (K), R37.1
unnamed: LD38.1 (K), R38.1
unnamed: LD39.1 (K), R39.1
unnamed: LD40.1 (K), R40.1
unnamed: LD41.1 (K), R41.1
unnamed: LD42.1 (K), R42.1
unnamed: LD43.1 (K), R43.1
unnamed: LD44.1 (K), R44.1
unnamed: LD45.1 (K), R45.1
unnamed: LD46.1 (K), R46.1
unnamed: LD47.1 (K), R47.1
unnamed: LD48.1 (K), R48.1
unnamed: LD49.1 (K), R49.1
unnamed: LD50.1 (K), R50.1
unnamed: LD51.1 (K), R51.1
unnamed: LD52.1 (K), R52.1
unnamed: LD53.1 (K), R53.1
unnamed: LD54.1 (K), R54.1
unnamed: LD55.1 (K), R55.1
unnamed: LD56.1 (K), R56.1
unnamed: LD57.1 (K), R57.1
unnamed: LD58.1 (K), R58.1
unnamed: LD59.1 (K), R59.1
unnamed: LD60.1 (K), R60.1
unnamed: LD61.1 (K), R61.1
unnamed: LD62.1 (K), R62.1
unnamed: LD63.1 (K), R63.1
unnamed: LD64.1 (K), R64.1
unnamed: LD65.1 (K), R65.1
unnamed: LD66.1 (K), R66.1
unnamed: LD67.1 (K), R67.1
unnamed: LD68.1 (K), R68.1
unnamed: LD69.1 (K), R69.1
unnamed: LD70.1 (K), R70.1
unnamed: LD71.1 (K), R71.1
unnamed: LD72.1 (K), R72.1
unnamed: LD73.1 (K), R73.1
unnamed: LD74.1 (K), R74.1
unnamed: LD75.1 (K), R75.1
unnamed: LD76.1 (K), R76.1
unnamed: LD77.1 (K), R77.1
unnamed: LD78.1 (K), R78.1
unnamed: LD79.1 (K), R79.1
unnamed: LD80.1 (K), R80.1
unnamed: LD81.1 (K), R81.1
unnamed: LD82.1 (K), R82.1
unnamed: LD83.1 (K), R83.1
unnamed: LD84.1 (K), R84.1
unnamed: LD85.1 (K), R85.1
unnamed: LD86.1 (K), R86.1
unnamed: LD87.1 (K), R87.1
unnamed: LD88.1 (K), R88.1
unnamed: LD89.1 (K), R89.1
unnamed: LD90.1 (K), R90.1
unnamed: LD91.1 (K), R91.1
unnamed: LD92.1 (K), R92.1
unnamed: LD93.1 (K), R93.1
unnamed: LD94.1 (K), R94.1
unnamed: LD95.1 (K), R95.1
unnamed: LD96.1 (K), R96.1
unnamed: LD97.1 (K), R97.1
unnamed: LD98.1 (K), R98.1
unnamed: LD99.1 (K), R99.1
unnamed: LD100.1 (K), R100.1
unnamed: LD101.1 (K), R101.1
unnamed: LD102.1 (K), R102.1
unnamed: LD103.1 (K), R103.1
unnamed: LD104.1 (K), R104.1

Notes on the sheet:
KEY MATRIX (6 rows x 21 cols, COL2ROW, 1N4148W per key)
PER-KEY BACKLIGHT (3 mm LED + 1k per key, PWM sink Q1)
MCU RP2040 + 16 MB QSPI flash
USB-C / ESD / 3.3 V
BACKLIGHT DRIVER
LOCK INDICATORS

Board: 2 copper layers, 469 parts (247 on the bottom side), 266 nets, no tracks yet.

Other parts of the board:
H1, H2, H3, H4, H5, H6, H7, H8, H9, H10, H11, H12: M2; MountingHole_2.2mm_M2

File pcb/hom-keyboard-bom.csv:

Qty,Value,Footprint,References
108,1k,Resistor_SMD:R_0603_1608Metric,R1 R2 R3 R4 R5 R6 R7 R8 R9 R10 R11 R12 R13 R14 R15 R16 R17 R18 R19 R20 R21 R22 R23 R24 R25 R26 R27 R28 R29 R30 R31 R32 R33 R34 R35 R36 R37 R38 R39 R40 R41 R42 R43 R44 R45 R46 R47 R48 R49 R50 R51 R52 R53 R54 R55 R56 R57 R58 R59 R60 R61 R62 R63 R64 R65 R66 R67 R68 R69 R70 R71 R72 R73 R74 R75 R76 R77 R78 R79 R80 R81 R82 R83 R84 R85 R86 R87 R88 R89 R90 R91 R92 R93 R94 R95 R96 R97 R98 R99 R100 R101 R102 R103 R104 R105 R108 R114 R115
104,1N4148W,Diode_SMD:D_SOD-123,D1 D2 D3 D4 D5 D6 D7 D8 D9 D10 D11 D12 D13 D14 D15 D16 D17 D18 D19 D20 D21 D22 D23 D24 D25 D26 D27 D28 D29 D30 D31 D32 D33 D34 D35 D36 D37 D38 D39 D40 D41 D42 D43 D44 D45 D46 D47 D48 D49 D50 D51 D52 D53 D54 D55 D56 D57 D58 D59 D60 D61 D62 D63 D64 D65 D66 D67 D68 D69 D70 D71 D72 D73 D74 D75 D76 D77 D78 D79 D80 D81 D82 D83 D84 D85 D86 D87 D88 D89 D90 D91 D92 D93 D94 D95 D96 D97 D98 D99 D100 D101 D102 D103 D104
104,LED 3mm,LED_THT:LED_D3.0mm,LD1 LD2 LD3 LD4 LD5 LD6 LD7 LD8 LD9 LD10 LD11 LD12 LD13 LD14 LD15 LD16 LD17 LD18 LD19 LD20 LD21 LD22 LD23 LD24 LD25 LD26 LD27 LD28 LD29 LD30 LD31 LD32 LD33 LD34 LD35 LD36 LD37 LD38 LD39 LD40 LD41 LD42 LD43 LD44 LD45 LD46 LD47 LD48 LD49 LD50 LD51 LD52 LD53 LD54 LD55 LD56 LD57 LD58 LD59 LD60 LD61 LD62 LD63 LD64 LD65 LD66 LD67 LD68 LD69 LD70 LD71 LD72 LD73 LD74 LD75 LD76 LD77 LD78 LD79 LD80 LD81 LD82 LD83 LD84 LD85 LD86 LD87 LD88 LD89 LD90 LD91 LD92 LD93 LD94 LD95 LD96 LD97 LD98 LD99 LD100 LD101 LD102 LD103 LD104
86,MX switch,Button_Switch_Keyboard:SW_Cherry_MX_1.00u_PCB,SW1 SW2 SW3 SW4 SW5 SW6 SW7 SW8 SW9 SW10 SW11 SW12 SW13 SW14 SW15 SW16 SW17 SW18 SW19 SW20 SW21 SW22 SW23 SW24 SW25 SW26 SW27 SW28 SW29 SW31 SW32 SW33 SW34 SW35 SW36 SW37 SW39 SW40 SW41 SW42 SW43 SW44 SW45 SW46 SW47 SW48 SW49 SW50 SW52 SW53 SW54 SW55 SW56 SW57 SW60 SW61 SW62 SW63 SW64 SW65 SW66 SW67 SW68 SW69 SW70 SW72 SW73 SW74 SW76 SW77 SW78 SW79 SW80 SW81 SW82 SW83 SW84 SW85 SW87 SW88 SW89 SW90 SW100 SW101 SW102 SW104
10,100n,Capacitor_SMD:C_0603_1608Metric,C1 C2 C3 C4 C5 C6 C7 C9 C10 C14
7,MX switch,Button_Switch_Keyboard:SW_Cherry_MX_1.25u_PCB,SW92 SW93 SW94 SW96 SW97 SW98 SW99
3,1u,Capacitor_SMD:C_0603_1608Metric,C8 C11 C16
2,10k,Resistor_SMD:R_0603_1608Metric,R109 R113
2,10u,Capacitor_SMD:C_0805_2012Metric,C15 C17
2,22p,Capacitor_SMD:C_0603_1608Metric,C12 C13
2,27,Resistor_SMD:R_0603_1608Metric,R106 R107
2,5.1k,Resistor_SMD:R_0603_1608Metric,R110 R111
2,MX switch,Button_Switch_Keyboard:SW_Cherry_MX_1.50u_PCB,SW38 SW51
2,MX switch,Button_Switch_Keyboard:SW_Cherry_MX_2.00u_PCB,SW30 SW103
2,MX switch,Button_Switch_Keyboard:SW_Cherry_MX_2.00u_Vertical_PCB,SW58 SW91
2,MX switch,Button_Switch_Keyboard:SW_Cherry_MX_2.25u_PCB,SW71 SW75
1,100,Resistor_SMD:R_0603_1608Metric,R112
1,12MHz,Crystal:Crystal_SMD_3225-4Pin_3.2x2.5mm,Y1
1,500mA,Fuse:Fuse_1206_3216Metric,F1
1,AO3400A,Package_TO_SOT_SMD:SOT-23,Q1
1,AP2112K-3.3,Package_TO_SOT_SMD:SOT-23-5,U4
1,BOOT,Button_Switch_SMD:SW_SPST_TL3342,SW105
1,CapsLock,LED_THT:LED_D3.0mm,LD106
1,MX switch,Button_Switch_Keyboard:SW_Cherry_MX_1.75u_PCB,SW59
1,MX switch,Button_Switch_Keyboard:SW_Cherry_MX_2.75u_PCB,SW86
1,MX switch,Button_Switch_Keyboard:SW_Cherry_MX_6.25u_PCB,SW95
1,NumLock,LED_THT:LED_D3.0mm,LD105
1,RESET,Button_Switch_SMD:SW_SPST_TL3342,SW106
1,RP2040,Package_DFN_QFN:QFN-56-1EP_7x7mm_P0.4mm_EP3.2x3.2mm_ThermalVias,U1
1,SWD,Connector_PinHeader_2.54mm:PinHeader_1x03_P2.54mm_Vertical,J2
1,USB-C,Connector_USB:USB_C_Receptacle_HRO_TYPE-C-31-M-12,J1
1,USBLC6-2SC6,Package_TO_SOT_SMD:SOT-23-6,U3
1,W25Q128JVS,Package_SO:SOIC-8_5.23x5.23mm_P1.27mm,U2

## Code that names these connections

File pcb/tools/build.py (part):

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    rp_pins[p] = "+3V3"
for p in ("23", "50", "45"):
    rp_pins[p] = "+1V1"
rp_pins.update({"57": "GND", "19": "GND", "20": "XIN", "21": "XOUT_MCU",
                "24": "SWCLK", "25": "SWDIO", "26": "RUN",
                "46": "USB_DM_MCU", "47": "USB_DP_MCU",
                "51": "QSPI_SD3", "52": "QSPI_SCLK", "53": "QSPI_SD0",
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    if c.ref in POS:
        c.pcb = POS[c.ref]

# crystal beyond the XIN/XOUT pins
n_x, _ = side_of("20")
mid = ((MCU_PADS["20"][0] + MCU_PADS["21"][0]) / 2, (MCU_PADS["20"][1] + MCU_PADS["21"][1]) / 2)
xt = (mid[0] + n_x[0] * 10.5 if n_x[0] else mid[0], mid[1] + n_x[1] * 10.5 if n_x[1] else mid[1])
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
# ---- lock indicators (THT LEDs on top) -----------------------------------------
ind_sch_x = 495.3
for i, (net, label) in enumerate((("LED_NUM", "NumLock"), ("LED_CAPS", "CapsLock"))):
    r_ind = nref("R")
    a_net = net + "_A"
    add(r_ind, "Device:R", "1k", "Resistor_SMD:R_0603_1608Metric", {"1": net, "2": a_net},
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                        "rows": [gp("ROW%d" % r) for r in range(NROWS)]},
        "features": {"bootmagic": True, "extrakey": True, "mousekey": False,
                     "nkro": True, "backlight": True},
        "backlight": {"driver": "pwm", "pin": gp("BL_PWM"), "levels": 6, "breathing": True},
        "indicators": {"caps_lock": gp("LED_CAPS"), "num_lock": gp("LED_NUM"), "on_state": 1},
        "layouts": {"LAYOUT_fullsize_ansi": {"layout": layout}},
    }
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    with open(os.path.join(out, "mcuconf.h"), "w") as f:
        f.write("#pragma once\n#include_next <mcuconf.h>\n\n"
                "// Backlight PWM\n#undef RP_PWM_USE_PWM%d\n#define RP_PWM_USE_PWM%d TRUE\n"
                % ((GPIO_OF["BL_PWM"] // 2) % 8, (GPIO_OF["BL_PWM"] // 2) % 8))
    with open(os.path.join(out, "halconf.h"), "w") as f:
        f.write("#pragma once\n#define HAL_USE_PWM TRUE\n#include_next <halconf.h>\n")
    with open(os.path.join(out, "config.h"), "w") as f:
        f.write("#pragma once\n\n#define BACKLIGHT_PWM_DRIVER PWMD%d\n#define BACKLIGHT_PWM_CHANNEL RP2040_PWM_CHANNEL_%s\n"
                "#define RP2040_BOOTLOADER_DOUBLE_TAP_RESET\n"
                % ((GPIO_OF["BL_PWM"] // 2) % 8, "A" if GPIO_OF["BL_PWM"] % 2 == 0 else "B"))


def write_project():
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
